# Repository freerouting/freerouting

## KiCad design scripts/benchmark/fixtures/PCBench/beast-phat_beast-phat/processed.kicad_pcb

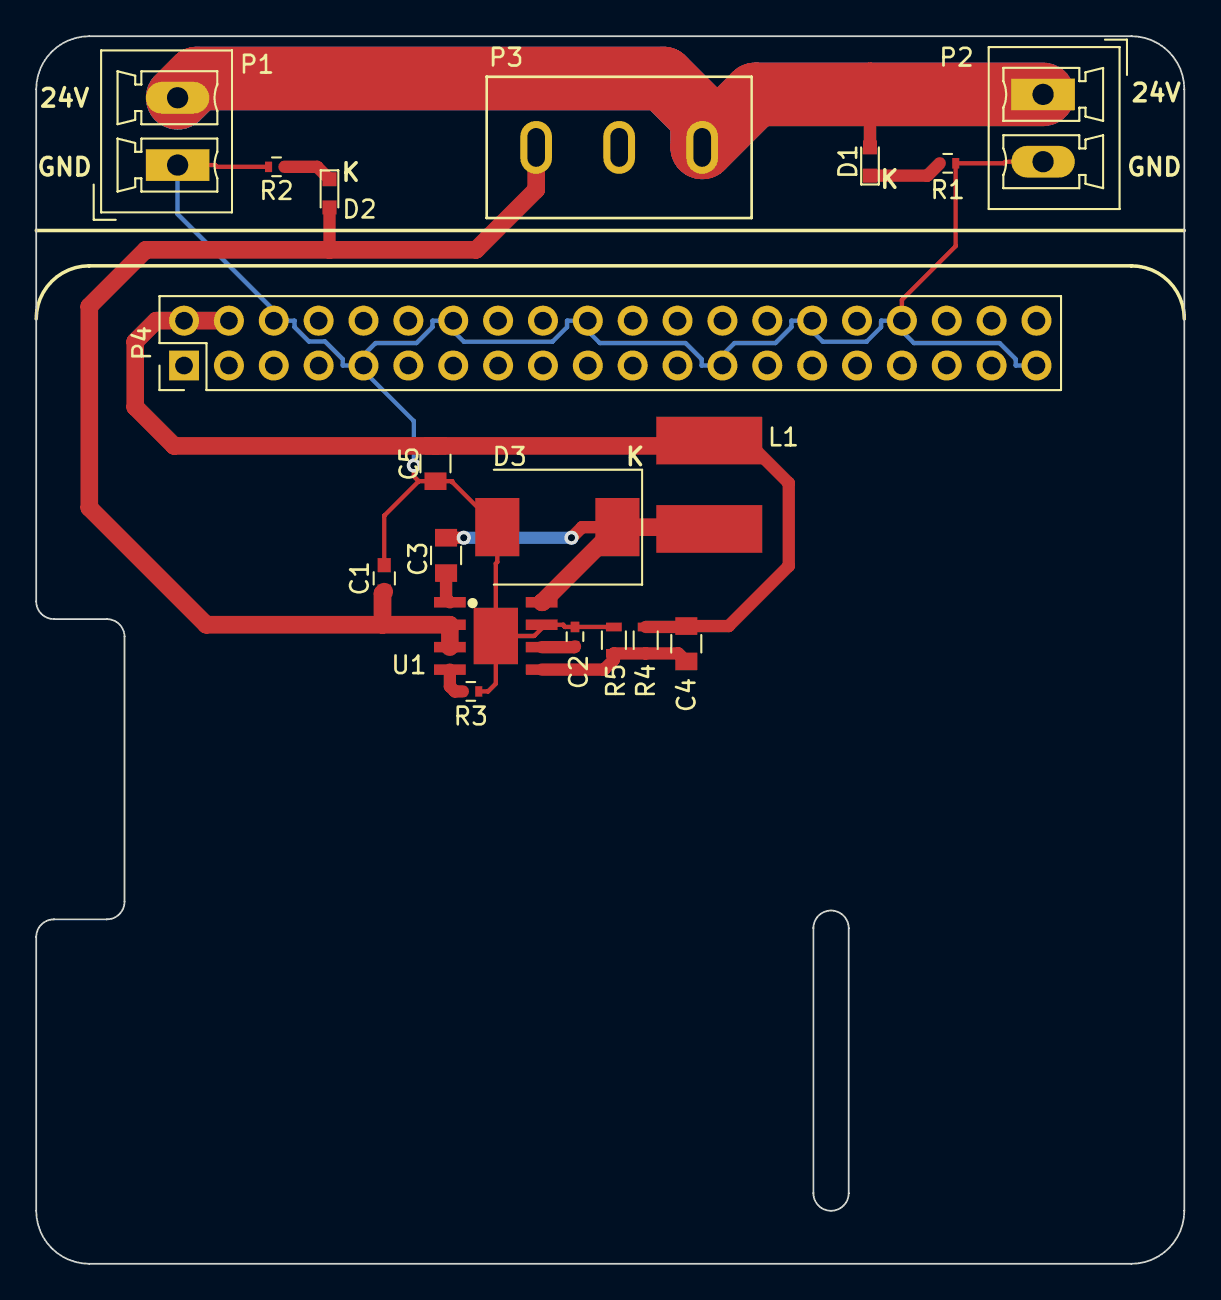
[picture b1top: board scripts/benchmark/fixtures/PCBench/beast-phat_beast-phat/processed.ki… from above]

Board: 2 copper layers, 65.0 x 69.5 mm, 19 parts (0 on the bottom side), 11 nets.

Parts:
C1: 4.7u; C_0603
C2: 8.2n; C_0402
C3: 100n; C_0805
C4: 120p; C_0805
C5: 47u; C_0805
D1, D2: LED; LED_0603
D3: SCHOTTKY; D_SMC_Standard
L1: 3.3u; SRN6045
P1: INPUT; PhoenixContact_MCV-G_02x3.81mm_Vertical
P2: OUTPUT; PhoenixContact_MCV-G_02x3.81mm_Vertical
P3: SWITCH; switch
P4: STACKING HEADER; Pin_Header_Straight_2x20_Pitch2.54mm
R1: 90K; R_0402
R2: 10K; R_0402
R3: 20K; R_0402
R4: 68K; R_0603
R5: 12K; R_0603
U1: LMR14030S; HSOP8

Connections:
/5V: C4.2, C5.2, L1.1, P4.2, P4.4, R4.1
GND: C1.1, C2.1, C5.1, D3.2, P1.1, P2.2, P4.6, P4.9, P4.14, P4.20, P4.25, P4.30, P4.34, P4.39, R1.2, R2.2, R3.2, R5.2, U1.7, U1.9
unnamed: C1.2, D2.2, P3.1, U1.2, U1.3
unnamed: C2.2, U1.6
unnamed: C3.1, D3.1, L1.2, U1.8
unnamed: C3.2, U1.1
unnamed: C4.1, R4.2, R5.1, U1.5
unnamed: D1.1, R1.1
unnamed: D1.2, P1.2, P2.1, P3.3
unnamed: D2.1, R2.1
unnamed: R3.1, U1.4

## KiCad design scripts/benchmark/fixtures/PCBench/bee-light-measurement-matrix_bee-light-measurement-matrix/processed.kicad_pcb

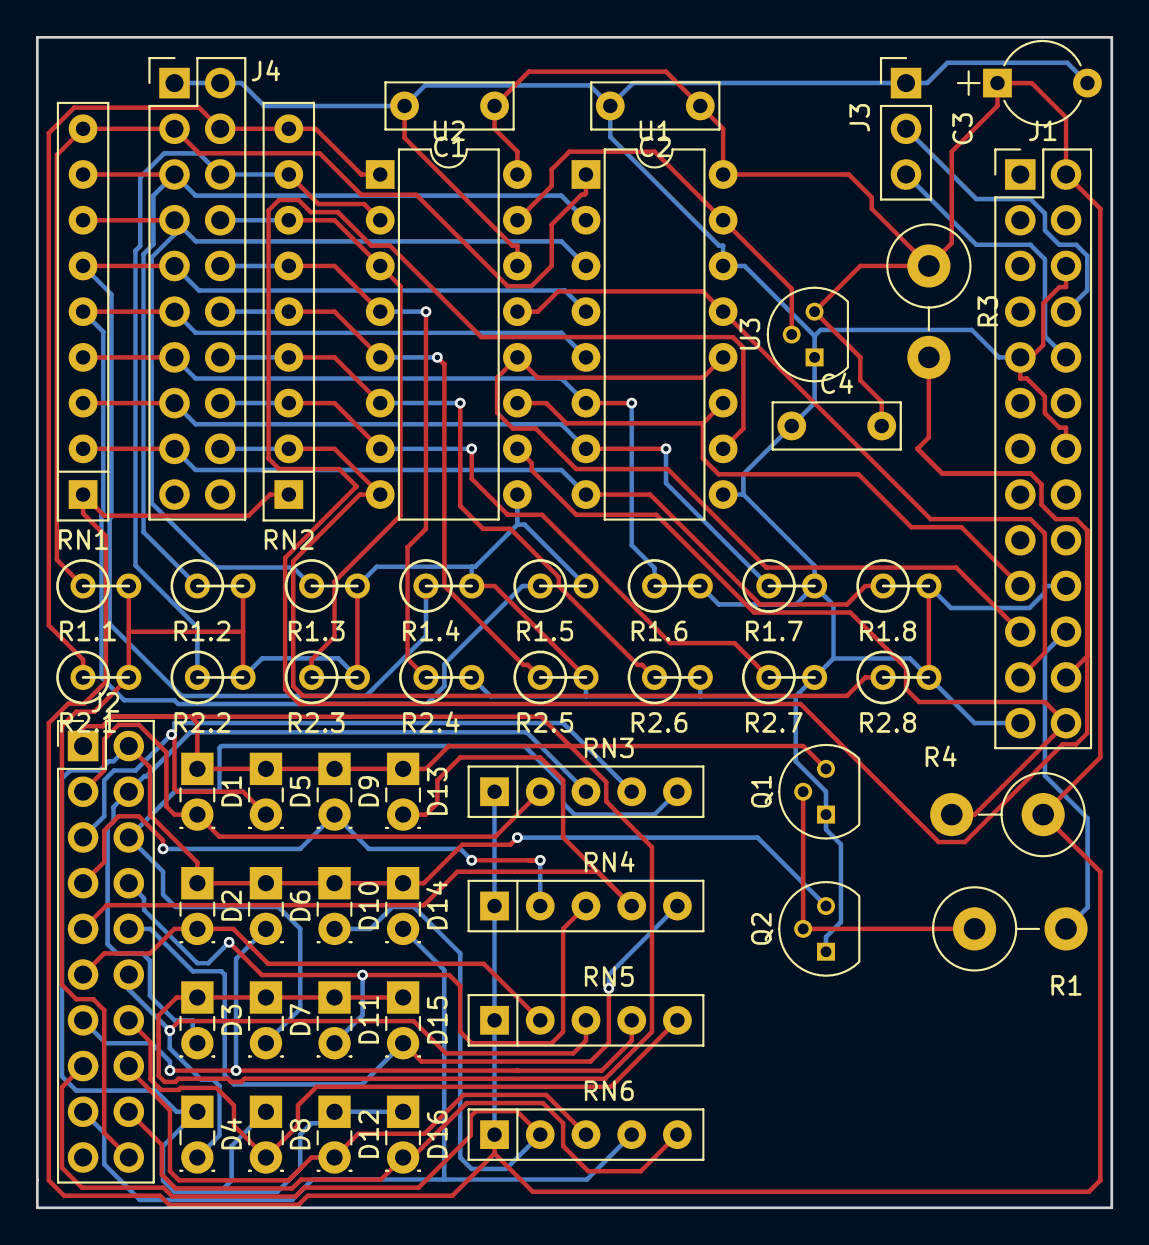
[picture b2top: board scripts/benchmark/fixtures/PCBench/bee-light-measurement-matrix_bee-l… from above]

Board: 2 copper layers, 59.7 x 65.0 mm, 54 parts (0 on the bottom side), 46 nets.

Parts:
C1, C2, C4: 100n; C_Disc_D7.0mm_W2.5mm_P5.00mm
C3: 10µ; CP_Radial_Tantal_D4.5mm_P5.00mm
D1, D2, D3, D4, D5, D6, D7, D8, D9, D10, D11, D12, D13, D14, D15, D16: LED; LED_Rectangular_W3.9mm_H1.8mm_FlatTop
J1: CONN_02X13; Pin_Header_Straight_2x13_Pitch2.54mm
J2, J4: CONN_02X10; Pin_Header_Straight_2x10_Pitch2.54mm
J3: CONN_01X03; Pin_Header_Straight_1x03_Pitch2.54mm
Q1, Q2: 2N3904; TO-92_Molded_Narrow
R1: 4,7k; R_Axial_DIN0414_L11.9mm_D4.5mm_P5.08mm_Vertical
R1.1, R1.2, R1.3, R1.4, R1.5, R1.6, R1.7, R1.8, R2.1, R2.2, R2.3, R2.4, R2.5, R2.6, R2.7, R2.8: R_PHOTO; R1
R3, R4: 100k; R_Axial_DIN0414_L11.9mm_D4.5mm_P5.08mm_Vertical
RN1, RN2: R_Network08; R_Array_SIP9
RN3, RN4, RN5, RN6: R_Network04; R_Array_SIP5
U1, U2: MCP3208; DIP-16_W7.62mm
U3: MCP1541; TO-92_Molded_Narrow

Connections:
+5V: C1.1, C2.1, C3.1, C4.2, J1.2, R3.1, R4.1, RN1.1, RN2.1, RN3.1, RN4.1, RN5.1, RN6.1, U1.16, U2.16, U3.3
CE0: J1.24, R3.2, U1.10
CE1: J1.26, R4.2, U2.10
CLK: J1.23, U1.13, U2.13
GND: C1.2, C2.2, C3.2, C4.1, J1.6, J1.9, J1.14, J1.20, J1.25, J2.20, J3.1, J4.1, J4.2, Q1.1, Q2.1, R1.1.2, R1.2.2, R1.3.2, R1.4.2, R1.5.2, R1.6.2, R1.7.2, R1.8.2, R2.1.2, R2.2.2, R2.3.2, R2.4.2, R2.5.2, R2.6.2, R2.7.2, R2.8.2, U1.9, U1.14, U2.9, U2.14, U3.1
GPIO25: J1.22, R1.2
LED_D1: D1.1, D3.1, D5.1, D7.1, D9.1, D11.1, D13.1, D15.1, J2.1, Q1.3
LED_D1_1: D1.2, J2.3, RN3.2
LED_D1_2: D3.2, J2.4, RN3.3
LED_D1_3: D5.2, J2.5, RN3.4
LED_D1_4: D7.2, J2.6, RN3.5
LED_D1_5: D9.2, J2.7, RN4.2
LED_D1_6: D11.2, J2.8, RN4.3
LED_D1_7: D13.2, J2.9, RN4.4
LED_D1_8: D15.2, J2.10, RN4.5
LED_D2: D2.1, D4.1, D6.1, D8.1, D10.1, D12.1, D14.1, D16.1, J2.2, Q2.3
LED_D2_1: D2.2, J2.11, RN5.2
LED_D2_2: D4.2, J2.12, RN5.3
LED_D2_3: D6.2, J2.13, RN5.4
LED_D2_4: D8.2, J2.14, RN5.5
LED_D2_5: D10.2, J2.15, RN6.2
LED_D2_6: D12.2, J2.16, RN6.3
LED_D2_7: D14.2, J2.17, RN6.4
LED_D2_8: D16.2, J2.18, RN6.5
MISO: J1.21, U1.12, U2.12
MOSI: J1.19, U1.11, U2.11
unnamed: J4.3, R1.1.1, RN1.9, U1.1
unnamed: J4.4, R2.1.1, RN2.9, U2.1
unnamed: J4.5, R1.2.1, RN1.8, U1.2
unnamed: J4.6, R2.2.1, RN2.8, U2.2
unnamed: J4.7, R1.3.1, RN1.7, U1.3
unnamed: J4.8, R2.3.1, RN2.7, U2.3
unnamed: J4.9, R1.4.1, RN1.6, U1.4
unnamed: J4.10, R2.4.1, RN2.6, U2.4
unnamed: J4.11, R1.5.1, RN1.5, U1.5
unnamed: J4.12, R2.5.1, RN2.5, U2.5
unnamed: J4.13, R1.6.1, RN1.4, U1.6
unnamed: J4.14, R2.6.1, RN2.4, U2.6
unnamed: J4.15, R1.7.1, RN1.3, U1.7
unnamed: J4.16, R2.7.1, RN2.3, U2.7
unnamed: J4.17, R1.8.1, RN1.2, U1.8
unnamed: J4.18, R2.8.1, RN2.2, U2.8
unnamed: Q1.2, Q2.2, R1.1
RXD: J1.10, J3.3
TXD: J1.8, J3.2
Vref: U1.15, U2.15, U3.2

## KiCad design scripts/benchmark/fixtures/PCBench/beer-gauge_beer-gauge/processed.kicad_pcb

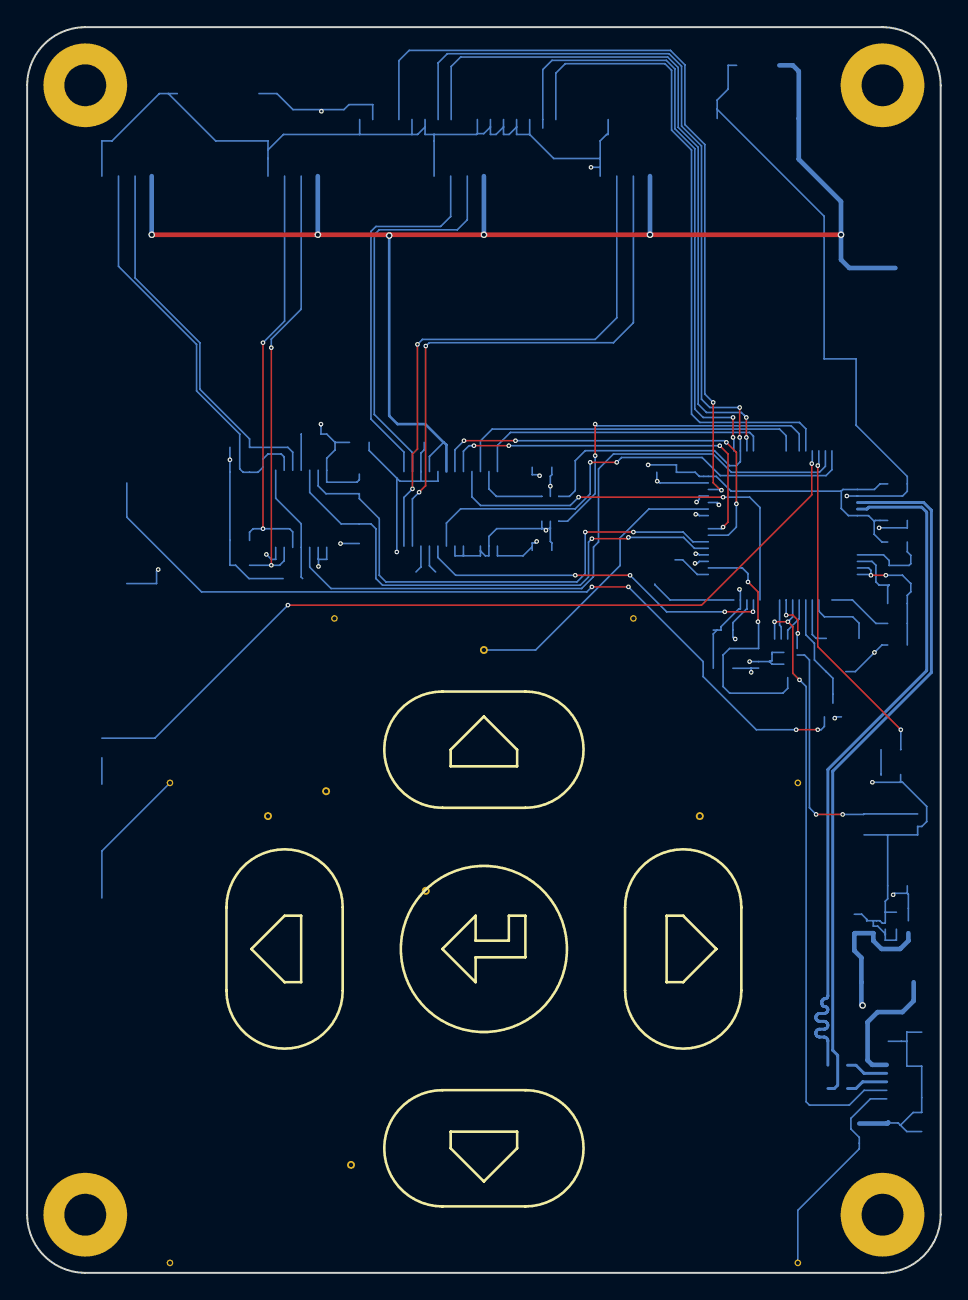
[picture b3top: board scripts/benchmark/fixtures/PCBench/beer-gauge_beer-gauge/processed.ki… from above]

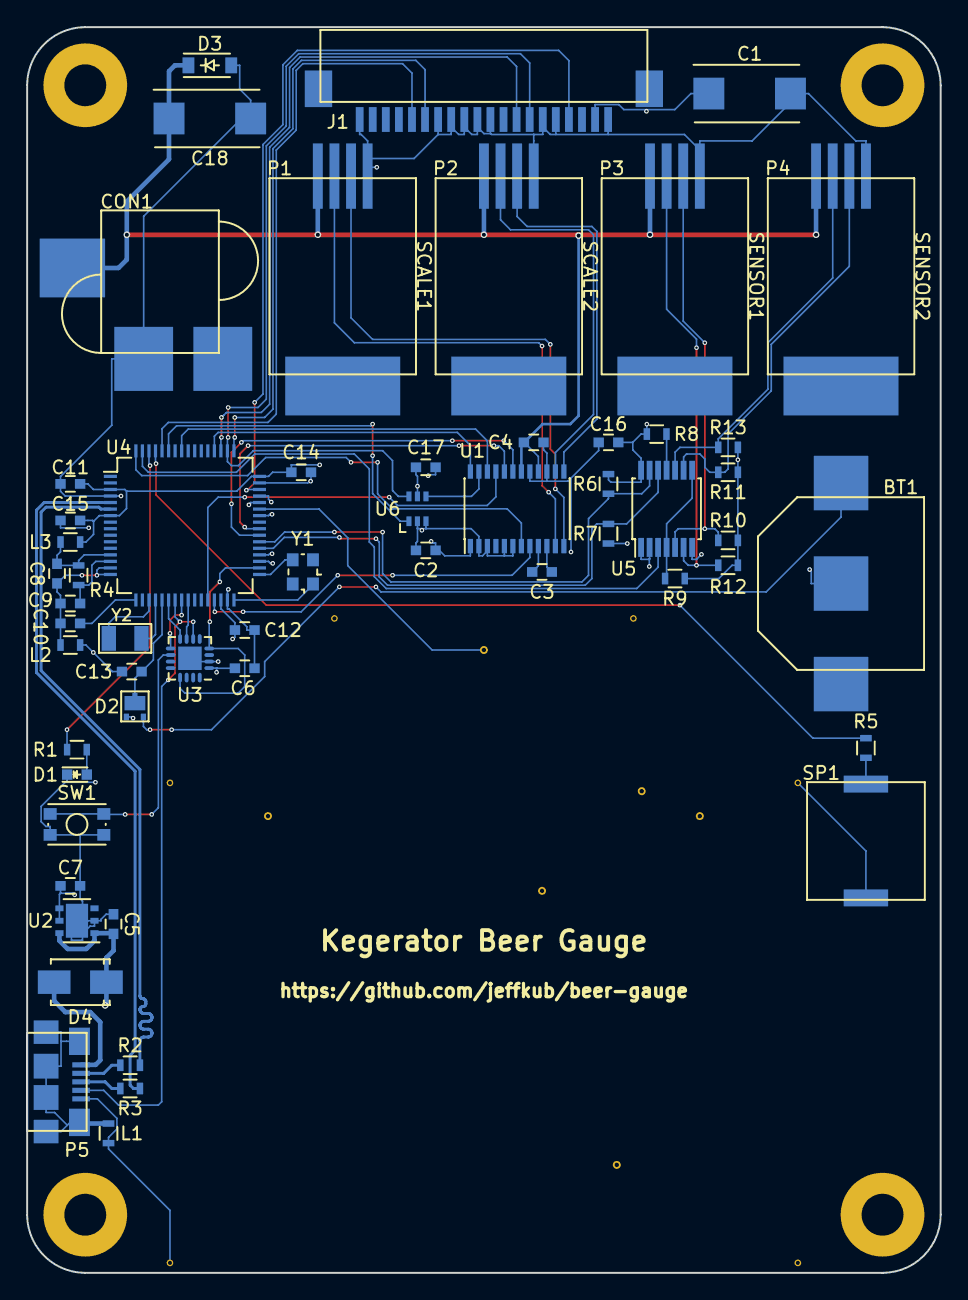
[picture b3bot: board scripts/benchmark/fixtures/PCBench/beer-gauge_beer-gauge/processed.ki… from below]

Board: 4 copper layers, 69.8 x 95.2 mm, 62 parts (56 on the bottom side), 64 nets.

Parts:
BT1: Battery; BK-885
C1: 220u; TantalC_SizeD_EIA-7343_Reflow
C2, C3, C4, C6, C9, C10, C11, C12, C13, C14, C16, C17: 0.1u; C_0603
C5, C7, C8, C15: 2.2u; C_0603
C18: 100u; TantalC_SizeD_EIA-7343_Reflow
CON1: BARREL_JACK; PJ-070AH-SMT
D1: LED; LED_0603
D2: PMEG4010CPA; SOT1061
D3: DDZ6V2B; SOD-123
D4: S1B; SMA_Standard
J1: OLED_MODULE; 0522712069
L1, L3: 600 Ohm/100 MHz; R_0603
L2: 600 Ohm/100 Mhz; R_0603
P1, P2, P3, P4: CONN_01X04; 0855135016
P5: USB_OTG; 10118192
R1, R4, R5: 470; R_0603
R2, R3: 33; R_0603
R6, R7, R8, R9, R10, R11, R12, R13: 4.7k; R_0603
SP1: PIEZO; PKMCS
SW1: SW_PUSH; SW_SPST_KMR2
U1: ADS1232; TSSOP-24_4.4x7.8mm_Pitch0.65mm
U2: LP38691; DFN-6-1EP_3x3mm_Pitch0.95mm
U3: MKL02Z32; QFN-16-1EP_3x3mm_Pitch0.5mm
U4: MK20DX256VLH7; LQFP-64_10x10mm_Pitch0.5mm
U5: TCA9543A; TSSOP-14_4.4x5mm_Pitch0.65mm
U6: SN74LVC1G58; SC-70-6
W1, W2, W3, W4, W5, W6: TEST_1P; PadVia
Y1: 16 MHz; Crystal_SMD_2520_4Pads
Y2: 32.768 kHz; ABS07

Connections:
+3V3: C1.1, C2.1, C6.1, C7.1, C11.1, C12.1, C14.1, C15.1, C16.1, C17.1, D2.2, J1.2, L3.1, R6.1, R7.1, R8.1, R9.1, R10.1, R11.1, R12.1, R13.1, U1.1, U2.4, U2.5, U3.1, U4.3, U4.7, U4.30, U4.48, U5.14, U6.5
+5V: C4.1, C5.1, C18.1, CON1.1, D3.1, D4.1, P1.1, P2.1, P3.1, P4.1, U1.16, U1.18, U2.1, U2.6
/Teensy/0: U1.19, U4.39
/Teensy/1: U1.20, U4.40
/Teensy/2: U1.22, U4.57
/Teensy/3: U1.21, U4.28
/Teensy/4: U1.8, U4.29
/Teensy/5: U1.7, U4.64
/Teensy/6: R5.2, U4.61
/Teensy/7: U4.59, U6.1
/Teensy/8: J1.16, U4.60
/Teensy/9: J1.4, U4.46
/Teensy/10: J1.15, U4.49
/Teensy/11: J1.8, U4.51
/Teensy/12: U1.24, U4.52
/Teensy/13: J1.7, U4.50, U6.6
/Teensy/15/A1: U4.43, W1.1
/Teensy/16/A2: U4.35, W2.1
/Teensy/17/A3: U4.36, W5.1
/Teensy/18/A4: R6.2, U4.38, U5.13
/Teensy/19/A5: R7.2, U4.37, U5.12
/Teensy/20/A6: R1.1, U4.62
/Teensy/21/A7: U4.63, U5.3
/Teensy/22/A8: U4.44, W3.1
/Teensy/23/A9: U4.45, W4.1
/Teensy/25: U4.42, W6.1
/Teensy/AREF: C9.1, R4.1, U4.14
/Teensy/ID: P5.4, U3.6, U4.23
/Teensy/RESET_B: U3.4, U3.13, U4.34
/Teensy/SWD_CLK: U3.8, U4.22
/Teensy/SWD_DIO: U3.7, U4.25
/Teensy/USB_D+: R3.1, U4.5
/Teensy/USB_D-: R2.1, U4.6
GND: BT1.2, C1.2, C2.2, C4.2, C5.2, C6.2, C7.2, C11.2, C12.2, C13.2, C14.2, C15.2, C16.2, C17.2, C18.2, CON1.2, D1.1, D3.2, J1.1, J1.5, J1.6, J1.10, J1.11, J1.12, J1.13, J1.14, J1.20, L1.2, L2.1, P1.4, P2.4, P3.4, P4.4, P5.5, SP1.2, SW1.1, U1.2, U1.3, U1.5, U1.6, U1.15, U1.17, U2.2, U2.7, U3.2, U3.17, U4.4, U4.31, U4.47, U5.1, U5.2, U5.7, U6.2, U6.3
unnamed: BT1.1, D2.1
unnamed: C3.1, U1.9
unnamed: C3.2, U1.10
unnamed: C8.1, L3.2, R4.2, U4.13
unnamed: C10.1, U4.17
unnamed: C8.2, C9.2, C10.2, L2.2, U4.15, U4.16
unnamed: C13.1, D2.3, U4.21
unnamed: D1.2, R1.2
unnamed: D4.2, P5.1
unnamed: L1.1, P5.6
unnamed: P1.2, U1.11
unnamed: P1.3, U1.12
unnamed: P2.2, U1.14
unnamed: P2.3, U1.13
unnamed: P3.2, R12.2, U5.6
unnamed: P3.3, R10.2, U5.5
unnamed: P4.2, R13.2, U5.10
unnamed: P4.3, R11.2, U5.9
unnamed: P5.2, R2.2
unnamed: P5.3, R3.2
unnamed: R5.1, SP1.1
unnamed: R8.2, U5.11
unnamed: R9.2, U5.4, U5.8
unnamed: SW1.2, U3.10
unnamed: U1.23, U6.4
unnamed: U3.9, U4.24
unnamed: U4.19, Y2.1
unnamed: U4.20, Y2.2
unnamed: U4.32, Y1.1
unnamed: U4.33, Y1.2
